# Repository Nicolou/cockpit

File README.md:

# cockpit
Came from this blog site : http://nicolasmontarnal.blogspot.fr

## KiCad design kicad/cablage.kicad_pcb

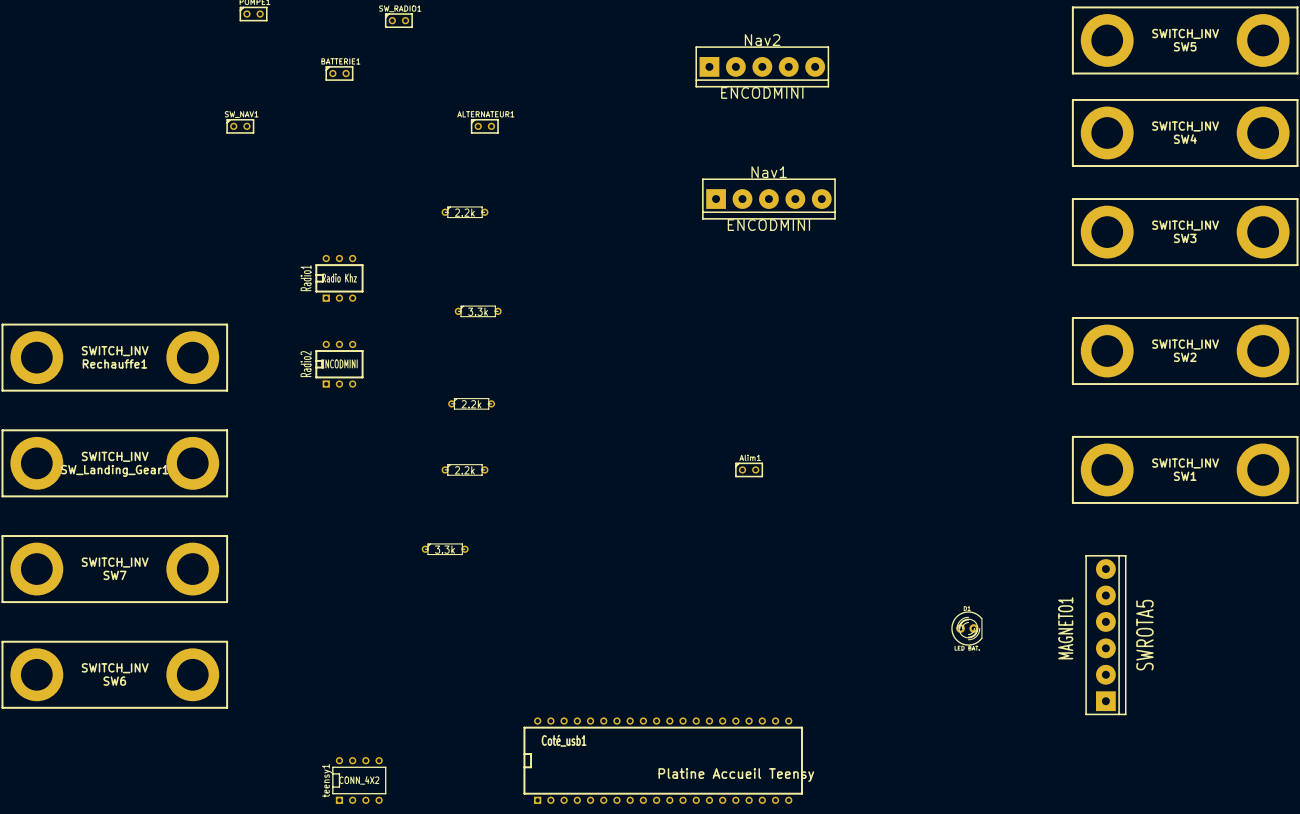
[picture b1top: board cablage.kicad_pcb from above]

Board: 2 copper layers, 28 parts (0 on the bottom side), 23 nets, no tracks yet.

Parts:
ALTERNATEUR1: SWITCH_INV; C1
Alim1: NAV.; C1
BATTERIE1: SWITCH_INV; C1
Coté_usb1: Platine Accueil Teensy; DIP-40__600
D1: LED BAT.; LED-5MM
MAGNETO1: SWROTA5; bornier6
Nav1, Nav2: ENCODMINI; bornier5
POMPE1: SWITCH_INV; C1
R1, R3, R5: 2.2k; R3
R2, R4: 3.3k; R3
Radio1: Radio Khz; DIP-6__300
Radio2: ENCODMINI; DIP-6__300
Rechauffe1: SWITCH_INV; 2PIN_6mm
SW1, SW2, SW3, SW4, SW5, SW6, SW7: SWITCH_INV; 2PIN_6mm
SW_Landing_Gear1: SWITCH_INV; 2PIN_6mm
SW_NAV1: SW_PUSH; C1
SW_RADIO1: SW_PUSH; C1
teensy1: CONN_4X2; DIP-8__300

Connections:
/e1: Radio2.1, teensy1.1
/e5: Nav2.1, teensy1.5
GND: ALTERNATEUR1.2, Alim1.1, BATTERIE1.2, Coté_usb1.1, Nav1.3, Nav1.4, Nav2.3, Nav2.4, POMPE1.2, Radio1.3, Radio1.4, Radio2.3, Radio2.4, Rechauffe1.2, SW1.2, SW2.2, SW3.2, SW4.2, SW5.2, SW6.2, SW7.2, SW_Landing_Gear1.2, SW_NAV1.1, SW_RADIO1.1
unnamed: Coté_usb1.23, MAGNETO1.3
unnamed: Coté_usb1.21, MAGNETO1.2
unnamed: Coté_usb1.19, MAGNETO1.1
unnamed: Coté_usb1.33, SW_RADIO1.2
unnamed: Coté_usb1.39, SW_NAV1.2
unnamed: Coté_usb1.27, MAGNETO1.5
unnamed: Coté_usb1.25, MAGNETO1.4
unnamed: Radio1.1, teensy1.8
unnamed: R4.1, Radio2.5
unnamed: R2.1, Radio1.5
unnamed: R1.1, R2.2, R3.1, R4.2
unnamed: Nav1.2, teensy1.2
unnamed: Nav1.1, teensy1.4
unnamed: D1.1, R5.1
unnamed: Alim1.2, Coté_usb1.14
unnamed: Coté_usb1.18, D1.2
unnamed: Radio2.2, teensy1.3
unnamed: Radio1.2, teensy1.6
unnamed: Nav2.2, teensy1.7
VCC: Coté_usb1.2, R5.2

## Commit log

2015-02-03 ajout de test encoder
2015-02-05 first add
2015-02-06 ﻿1.move file and delete subdirectory 2.debug flip navigation button.
    # Please enter the commit message for your changes. Lines starting
    # with '#' will be ignored, and an empty message aborts the commit.
    # On branch master
    # Your branch is up-to-date with 'origin/master'.
    #
    # Changes to be committed:
2015-02-06 changement de répertoire pour une ouverture reussi dans arduino
2016-02-13 create Aquila
2016-02-13 add others buttons
2016-02-15 add swith to make more functionality to the knobs fonctionalities are : - transpopndeur values from knob 1 to 4 - altimeter bora setting - directional gyro setting - OBS VOR 1 setting
2016-02-15 add command light intruments switch
